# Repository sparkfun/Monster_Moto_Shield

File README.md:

Monster Moto Shield
===================

This motor shield contains a pair of VNH2SP30 full-bridge motor drivers, pitched for the 5mm screw terminals. 

Features
-------------------
* Voltage max: 16V
* Maximum current rating: 30 A
* Practical Continuous Current: 14 A
* Current sensing available to Arduino analog pin
* MOSFET on-resistance: 19 mΩ (per leg)
* Maximum PWM frequency: 20 kHz
* Thermal Shutdown
* Undervoltage and Overvoltage shutdown

Repository Contents
-------------------
* **/Firmware** - Example Arduino sketch 
* **/Hardware** - All Eagle design files (.brd, .sch)
<!--- * **/Production** - Test bed files and production panel files
This folder doesn't actually resist, so I removed it from the README. --->

License Information
-------------------
The hardware is released under [Creative Commons ShareAlike 4.0 International](https://creativecommons.org/licenses/by-sa/4.0/).
The code is beerware; if you see the authors (or any SparkFun employee) at the local, and you've found our code helpful, please buy us a round!

Distributed as-is; no warranty is given.

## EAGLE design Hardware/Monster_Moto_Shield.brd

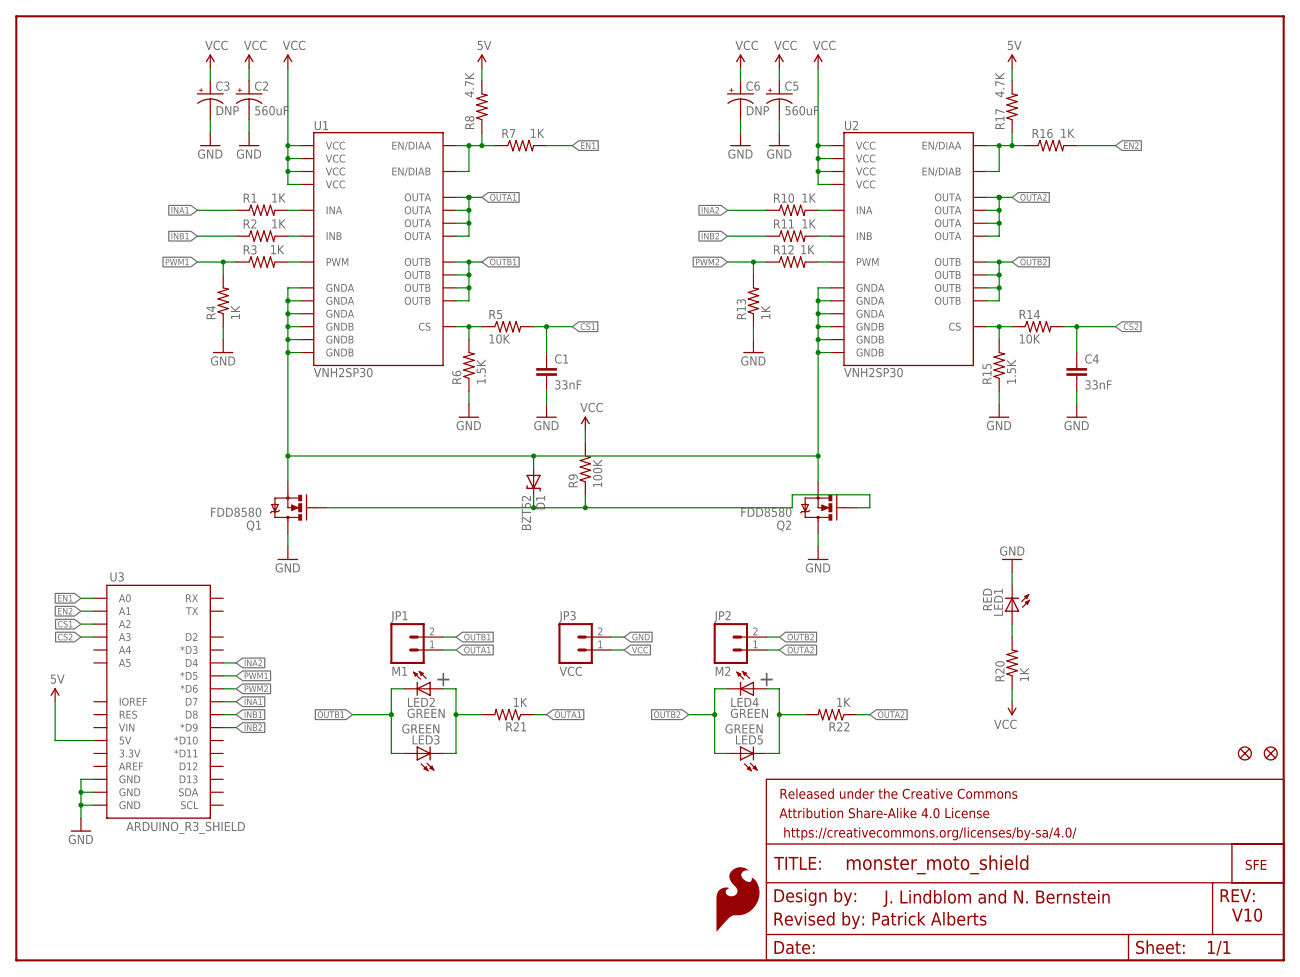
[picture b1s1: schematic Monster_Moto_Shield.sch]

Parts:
C1, C4: 33nF; 0603-CAP
C2, C5: 560uF; PANASONIC_G
C3, C6: DNP; CPOL-RADIAL-1000UF-25V
D1: BZT52; SOD-323
FRAME*: FRAME-LETTER; CREATIVE_COMMONS
JP1: M1; 1X02_XTRA_BIG
JP2: M2; 1X02_XTRA_BIG
JP3: VCC; 1X02_XTRA_BIG
JP4, JP6: FIDUCIAL1X2; FIDUCIAL-1X2
JP5: LOGO-SFENEW; SFE-NEW-WEBLOGO
LED1: RED; LED-0603
LED2, LED3, LED4, LED5: GREEN; LED-0603
LOGO1: SFE_LOGO_FLAME.2_INCH; SFE_LOGO_FLAME_.2
Q1, Q2: FDD8580; DPAK
R1, R2, R3, R4, R7, R10, R11, R12, R13, R16, R20, R21, R22: 1K; 0603-RES
R5, R14: 10K; 0603-RES
R6, R15: 1.5K; 0603
R8, R17: 4.7K; 0603
R9: 100K; 0603-RES
U1, U2: VNH2SP30
U3: ARDUINO_R3_SHIELD; UNO_R3_SHIELD

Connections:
5V: R8.2, R17.2, U3.5V
CS1: C1.1, R5.2, U3.A2
CS2: C4.1, R14.2, U3.A3
EN1: R7.2, U3.A0
EN2: R16.2, U3.A1
GND: C1.2, C2.-, C3.2 (-), C4.2, C5.-, C6.2 (-), JP3.2, LED1.C, Q1.4 (D), Q2.4 (D), R4.1, R6.1, R13.1, R15.1, U3.GND@0 (GND), U3.GND@1 (GND), U3.GND@2 (GND)
INA1: R1.1, U3.D7
INA2: R10.1, U3.D4
INB1: R2.1, U3.D8
INB2: R11.1, U3.D9 (*D9)
unnamed: R2.2, U1.11 (INB)
unnamed: R1.2, U1.5 (INA)
unnamed: R11.2, U2.11 (INB)
unnamed: R10.2, U2.5 (INA)
unnamed: R3.2, U1.8 (PWM)
unnamed: R12.2, U2.8 (PWM)
unnamed: R5.1, R6.2, U1.9 (CS)
unnamed: R14.1, R15.2, U2.9 (CS)
unnamed: R16.1, R17.1, U2.6 (EN/DIAA), U2.10 (EN/DIAB)
unnamed: D1.2 (A), Q1.3 (S), Q2.3 (S), U1.18 (GNDB), U1.19 (GNDB), U1.20 (GNDB), U1.26 (GNDA), U1.27 (GNDA), U1.28 (GNDA), U2.18 (GNDB), U2.19 (GNDB), U2.20 (GNDB), U2.26 (GNDA), U2.27 (GNDA), U2.28 (GNDA)
unnamed: R7.1, R8.1, U1.6 (EN/DIAA), U1.10 (EN/DIAB)
unnamed: D1.1 (C), Q1.1 (G), Q2.1 (G), R9.1
unnamed: LED2.A, LED3.C, R21.2
unnamed: LED4.A, LED5.C, R22.2
unnamed: LED1.A, R20.2
OUTA1: JP1.1, R21.1, U1.1 (OUTA), U1.25 (OUTA), U1.30 (OUTA), U1.SLUG3 (OUTA)
OUTA2: JP2.1, R22.1, U2.1 (OUTA), U2.25 (OUTA), U2.30 (OUTA), U2.SLUG3 (OUTA)
OUTB1: JP1.2, LED2.C, LED3.A, U1.15 (OUTB), U1.16 (OUTB), U1.21 (OUTB), U1.SLUG2 (OUTB)
OUTB2: JP2.2, LED4.C, LED5.A, U2.15 (OUTB), U2.16 (OUTB), U2.21 (OUTB), U2.SLUG2 (OUTB)
PWM1: R3.1, R4.2, U3.D5 (*D5)
PWM2: R12.1, R13.2, U3.D6 (*D6)
VCC: C2.+, C3.1 (+), C5.+, C6.1 (+), JP3.1, R9.2, R20.1, U1.3 (VCC), U1.13 (VCC), U1.23 (VCC), U1.SLUG1 (VCC), U2.3 (VCC), U2.13 (VCC), U2.23 (VCC), U2.SLUG1 (VCC)

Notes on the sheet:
J. Lindblom and N. Bernstein
Revised by: Patrick Alberts
V10

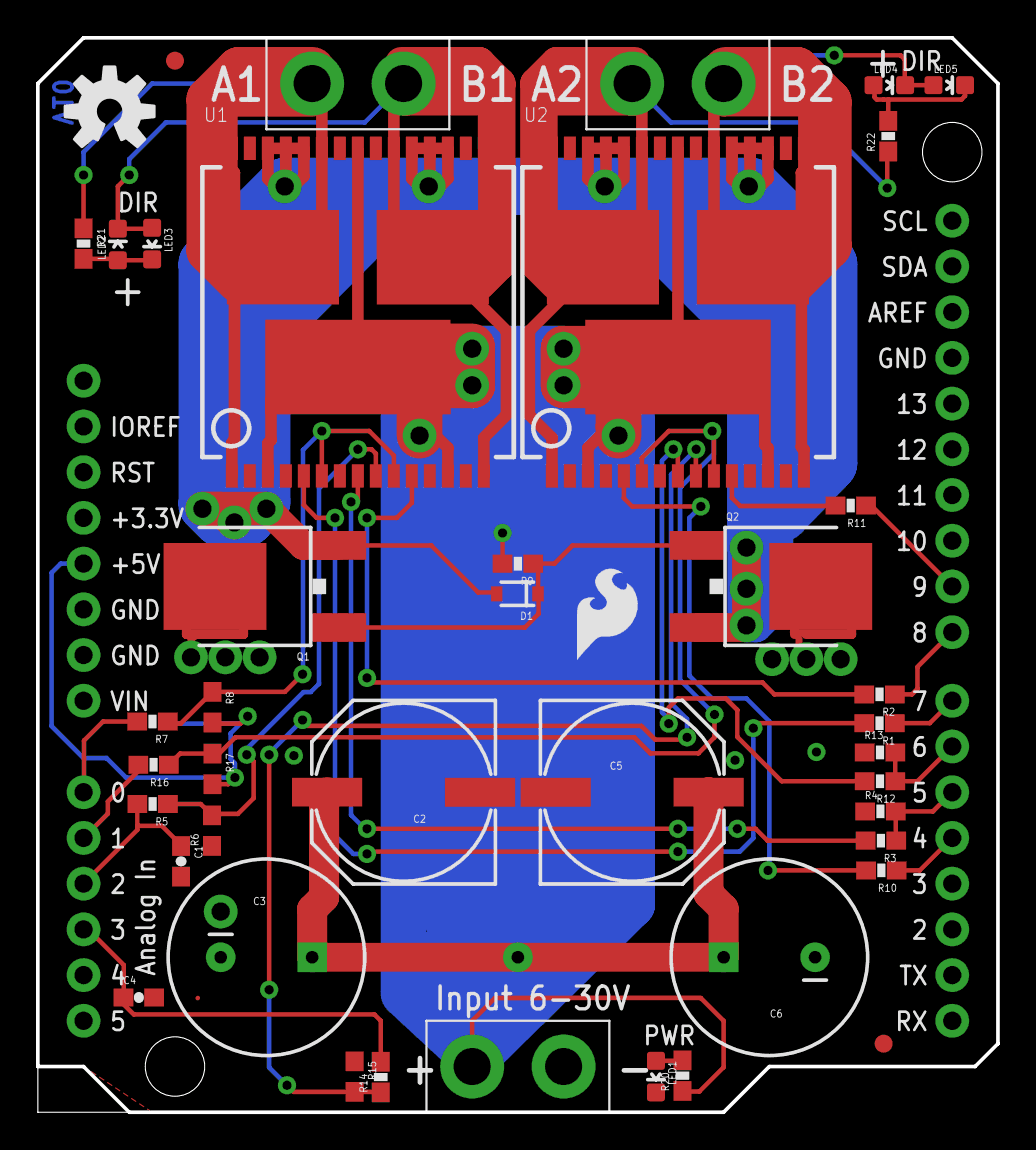
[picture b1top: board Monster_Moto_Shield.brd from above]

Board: 2 copper layers, 53.3 x 59.7 mm, 48 parts (1 on the bottom side), 32 nets.

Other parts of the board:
U$3: OSHW-LOGO-M
U$4, U$6: STAND-OFF

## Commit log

2014-05-06 Initial commit with brd/sch
2014-05-12 Changed to 0603
2014-05-12 Commit bec of computer change
2014-05-16 Computer Change
2014-05-16 Cleared Up Drc Isssues
2014-06-26 Added SF Flame, Cleaned Up SCH, Added Input v silk.
2014-08-07 Adding current board files and example sketch
2014-08-07 Adding rev files back in
2014-08-08 Chaned LED res to 1k
2014-10-09 Re up-ing for Transfer
2016-01-21 arguments to motorGo changed to uint8_t range
2019-10-07 Added explanatory comments to the code and improved it further.
2019-10-07 Updated code
2020-07-24 Modified to adhere to sparkfun standard practices
2020-07-24 Update README.md
    Removed the mention of a /Production folder since it doesn't exist, as well as fixed the embedded store link in the image.

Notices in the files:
parts and their libraries:
SparkFun-Resistors: Licensing: Creative Commons ShareAlike 4.0 International - https://creativecommons.org/licenses/by-sa/4.0
SparkFun-Aesthetics: Released under the Creative Commons Attribution Share-Alike 4.0 License
SparkFun-Aesthetics: Released under the Creative Commons
